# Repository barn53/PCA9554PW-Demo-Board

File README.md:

# PCA9554PW-Demo Board
 Demo board for PCA9554PW 8 I²C, SMBus I/O Expanders

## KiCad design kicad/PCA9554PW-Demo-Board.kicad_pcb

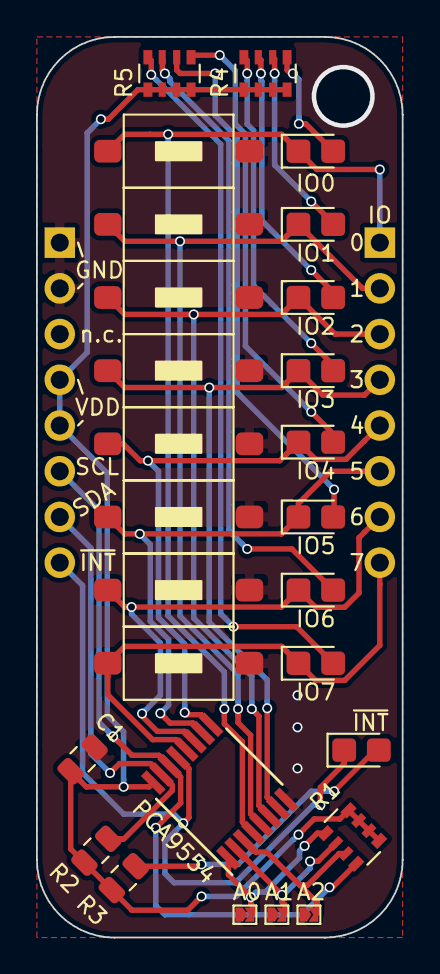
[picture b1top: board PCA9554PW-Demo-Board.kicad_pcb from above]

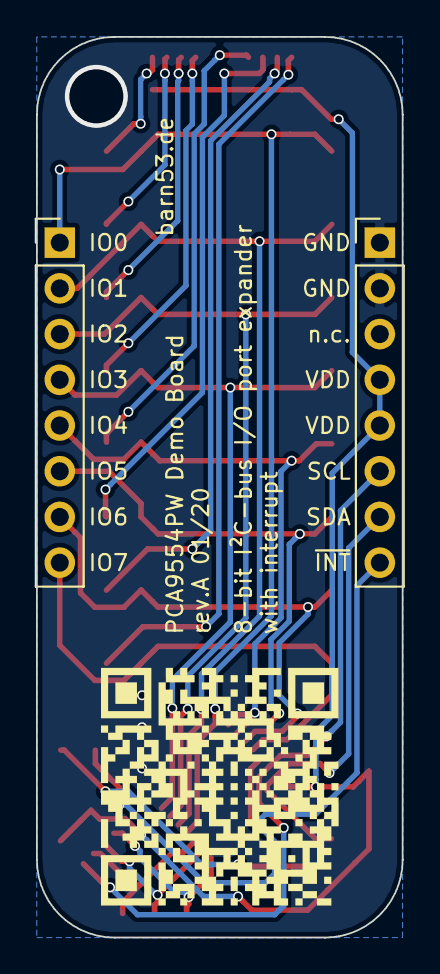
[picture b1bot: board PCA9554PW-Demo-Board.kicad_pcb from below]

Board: 2 copper layers, 20.3 x 50.0 mm, 30 parts (3 on the bottom side), 25 nets.

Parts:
C1: 100n; C_0805_2012Metric
D1: ~INT; LED_0805_2012Metric_Castellated
D2: IO0; LED_0805_2012Metric_Castellated
D3: IO1; LED_0805_2012Metric_Castellated
D4: IO2; LED_0805_2012Metric_Castellated
D5: IO3; LED_0805_2012Metric_Castellated
D6: IO4; LED_0805_2012Metric_Castellated
D7: IO5; LED_0805_2012Metric_Castellated
D8: IO6; LED_0805_2012Metric_Castellated
D9: IO7; LED_0805_2012Metric_Castellated
J1, J2: Conn_01x08; PinHeader_1x08_P2.54mm_Vertical
JP1: A0; SolderJumper-2_small
JP2: A1; SolderJumper-2_small
JP3: A2; SolderJumper-2_small
QR*****: QR_barn53.de
R1: 10k; R_Array_Convex_4x0603
R2: 10k; R_0805_2012Metric
R3: 220; R_0805_2012Metric
R4, R5: 220; R_Array_Convex_4x0603
SW1, SW2, SW3, SW4, SW5, SW6, SW7, SW8: SW_Push; SMD_Push_Button
U1: PCA9554; TSSOP-16_4.4x5mm_P0.65mm

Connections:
/A0: JP1.2, R1.1, U1.1
/A1: JP2.2, R1.2, U1.2
/A2: JP3.2, R1.3, U1.3
/IO0: D2.1, J2.1, SW1.1, U1.4
/IO1: D3.1, J2.2, SW2.1, U1.5
/IO2: D4.1, J2.3, SW3.1, U1.6
/IO3: D5.1, J2.4, SW4.1, U1.7
/IO4: D6.1, J2.5, SW5.1, U1.9
/IO5: D7.1, J2.6, SW6.1, U1.10
/IO6: D8.1, J2.7, SW7.1, U1.11
/IO7: D9.1, J2.8, SW8.1, U1.12
/SCL: J1.6, R1.4, U1.14
/SDA: J1.7, R2.2, U1.15
/~INT: D1.1, J1.8, U1.13
GND: C1.2, J1.1, J1.2, JP1.1, JP2.1, JP3.1, SW1.2, SW2.2, SW3.2, SW4.2, SW5.2, SW6.2, SW7.2, SW8.2, U1.8
unnamed: D1.2, R3.2
unnamed: D2.2, R4.1
unnamed: D3.2, R4.2
unnamed: D4.2, R4.3
unnamed: D5.2, R4.4
unnamed: D6.2, R5.1
unnamed: D7.2, R5.2
unnamed: D8.2, R5.3
unnamed: D9.2, R5.4
VDD: C1.1, J1.4, J1.5, R1.5, R1.6, R1.7, R1.8, R2.1, R3.1, R4.5, R4.6, R4.7, R4.8, R5.5, R5.6, R5.7, R5.8, U1.16

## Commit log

2020-01-07 Completed rev.A
2020-02-04 saving commit
2021-01-19 added source code
